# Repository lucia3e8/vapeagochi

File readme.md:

# tamagotchi that dies if you stop vaping
...has been rewritten in Rust. we also made it die if you _keep_ vaping. It counts how many times you've hit it and once you're at the dialy limit, turns off the heating coil.

## dirs
```
.
├── assets # animation sprites etc
├── case # fusion360 files for 3d-printed case
├── ee # kicad, components, assembly
├── readme.txt # you are here
├── scripts # one offs
├── vg2 # vestigial C++ stm32ide build
└── vgrs # new rust build <- USE THIS ONE
```

# Hardware
## Case
Initially we used a bc5000 vape because it's small and cute.
Right now bc5000 is too small to fit all the hardware, so we use a gimi30k instead.

Eventually I want to target the bc5000 because it's cuter but I'd have to redesign the PCB

## Pinout

```
| Pin  | Function        |
|------|-----------------|
| PA5  | SCREEN_CLK      |
| PA6  | SCREEN_RES      |
| PA7  | SCREEN_DIN      |
| PA8  | SCREEN_DC       |
| PB10 | SCREEN_CS       |
| PB3  | Left Button     |
| PA0  | Middle Button   |
| PB2  | Right Button    |
| PA4  | Coil Input      |
| PB11 | Coil Enable     |
| PA1  | Programmable LED|
```
By default, the vape's heating coil is disabled via a MOSFET. Pull `PB11 (Coil Enable)` high to allow the coil to turn on when user hits the vape.
When user tries to hit the vape, `PA4 (Coil Input)` will go high, regardless of `PB11` state.

# Software
## Building

Either use `nix-shell`, or manually install `cargo` with `thumbv6m-none-eabi` target and `probe-rs`.
```
cd vgrs
nix-shell
cargo build --release --target thumbv6m-none-eabi # build
sudo probe-rs run --chip STM32L072CBTx target/thumbv6m-none-eabi/release/vgrs # flash
```

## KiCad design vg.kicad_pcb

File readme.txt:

# Vapeagochi
## Building
linux only
run `mkdir -p build && make`
install stmcube programmer
run the programmer as root
under Erasing and Programming, pick your firmware.bin file
(you may have to first change the file owner to root because programmer is running as root)
set start address to 0x08000000
hit "Start Programming"

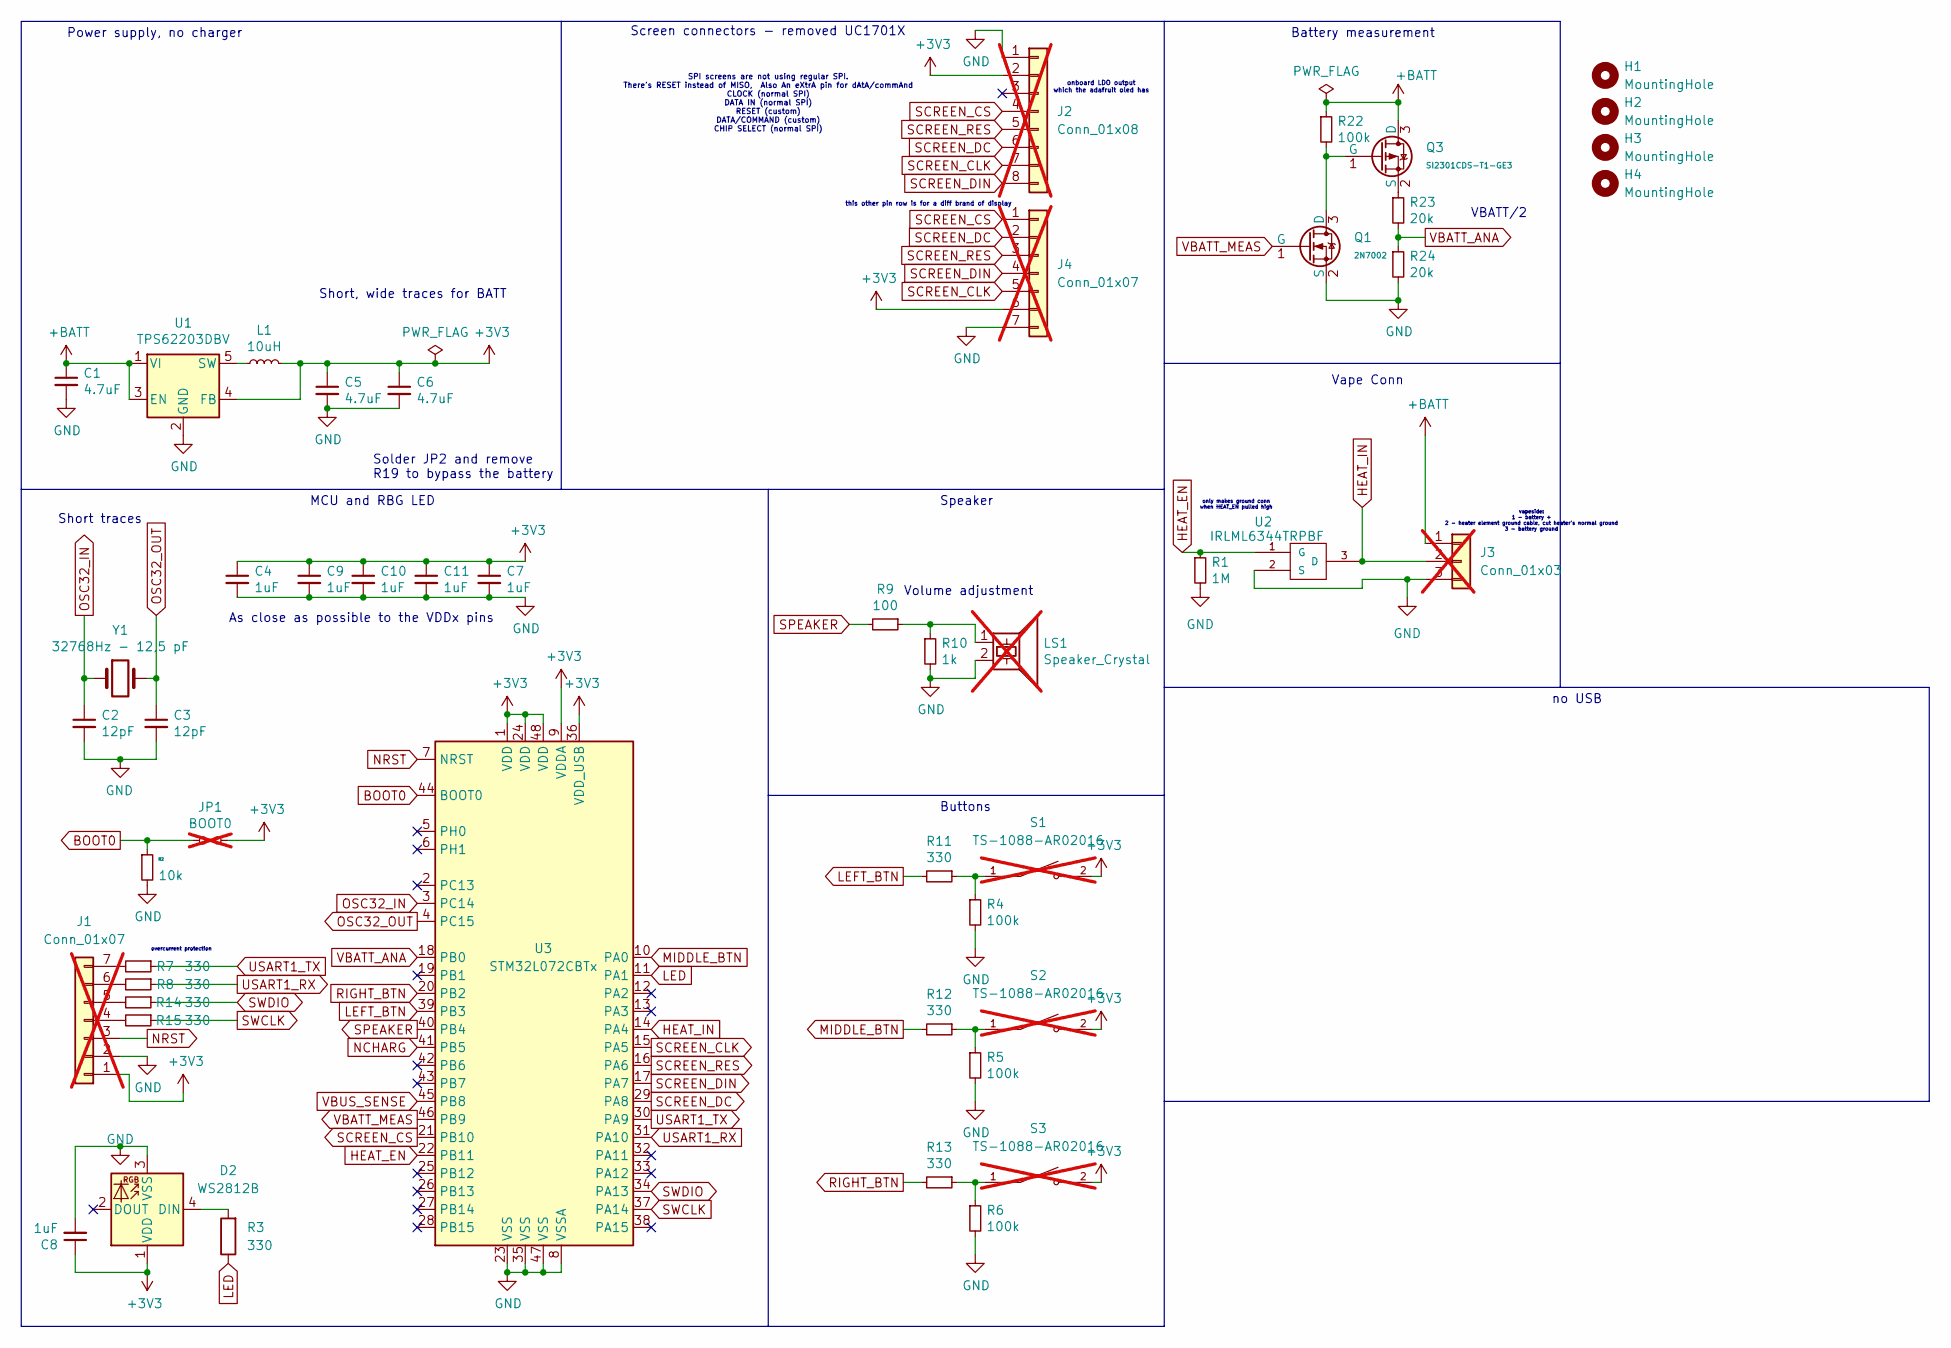
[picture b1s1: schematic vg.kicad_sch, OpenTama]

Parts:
C1, C5, C6: 4.7uF; C_0402_1005Metric; LCSC C23733
C2, C3: 12pF; C_0402_1005Metric; LCSC C1547
C4, C7, C8, C9, C10, C11: 1uF; C_0402_1005Metric; LCSC C52923
D2: WS2812B; LED_WS2812B_PLCC4_5.0x5.0mm_P3.2mm; LCSC C22461793
H1, H2, H3, H4: MountingHole; MountingHole_2.7mm_M2.5
J1, J4: Conn_01x07; PinHeader_1x07_P2.54mm_Vertical; not fitted
J2: Conn_01x08; PinHeader_1x08_P2.54mm_Vertical; not fitted
J3: Conn_01x03; JST_XH_S3B-XH-A_1x03_P2.50mm_Horizontal; not fitted
JP1: BOOT0; PinHeader_1x02_P2.54mm_Vertical; not fitted
L1: 10uH; L_0805_2012Metric; LCSC C1046
LS1: Speaker_Crystal; Buzzer_CUI_CPT-9019S-SMT; LCSC C391035; not fitted
Q1: 2N7002; Q_SOT-23; Part 2N7002; LCSC C8545
Q3: SI2301CDS-T1-GE3; Q_SOT-23; Part SI2301CDS-T1-GE3; LCSC C10487
R1: 1M; R_0402_1005Metric; LCSC C26083
R2: 10k; R_0402_1005Metric; LCSC C25744
R3: 330; R_0402_1005Metric
R4, R5, R6, R22: 100k; R_0402_1005Metric; LCSC C25741
R7, R8, R11, R12, R13, R14, R15: 330; R_0402_1005Metric; LCSC C25104
R9: 100; R_0805; LCSC C25076
R10: 1k; R_0402
R23, R24: 20k; R_0402_1005Metric; LCSC C25765
S1, S2, S3: TS-1088-AR02016; SW_TS-1088-AR02016; PARTREV N/A; LCSC C720477; not fitted
U1: TPS62203DBV; SOT-23-5; LCSC C9051
U2: IRLML6344TRPBF; SOT95P240X112-3N; MPN IRLML6344TRPBF
U3: STM32L072CBTx; LQFP-48_7x7mm_P0.5mm; LCSC C465977
Y1: 32768Hz - 12,5 pF; Crystal_SMD_3215-2Pin_3.2x1.5mm; LCSC C32346

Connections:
+3V3: C4.1, C5.1, C6.1, C7.1, C8.1, C9.1, C10.1, C11.1, D2.1 (VDD), J1.1, J2.2, J4.6, JP1.2, L1.2, S1.2, S2.2, S3.2, U1.4 (FB), U3.1 (VDD), U3.9 (VDDA), U3.24 (VDD), U3.36 (VDD_USB), U3.48 (VDD)
+BATT: C1.1, J3.1, Q3.3 (D), R22.1, U1.1 (VI), U1.3 (EN)
BOOT0: JP1.1, R2.1, U3.44 (BOOT0)
GND: C1.2, C2.2, C3.2, C4.2, C5.2, C6.2, C7.2, C8.2, C9.2, C10.2, C11.2, D2.3 (VSS), J1.2, J2.1, J3.3, J4.7, LS1.2, Q1.2 (S), R1.2, R2.2, R4.2, R5.2, R6.2, R10.2, R24.2, U1.2 (GND), U2.2 (S), U3.8 (VSSA), U3.23 (VSS), U3.35 (VSS), U3.47 (VSS)
HEAT_EN: R1.1, U2.1 (G), U3.22 (PB11)
HEAT_IN: J3.2, U2.3 (D), U3.14 (PA4)
LED: R3.1, U3.11 (PA1)
LEFT_BTN: R11.2, U3.39 (PB3)
MIDDLE_BTN: R12.2, U3.10 (PA0)
NCHARG: U3.41 (PB5)
NRST: J1.3, U3.7 (NRST)
unnamed: D2.4 (DIN), R3.2
unnamed: J1.4, R15.2
unnamed: J1.5, R14.2
unnamed: J1.6, R8.2
unnamed: J1.7, R7.2
unnamed: LS1.1, R9.1, R10.1
unnamed: Q1.3 (D), Q3.1 (G), R22.2
unnamed: Q3.2 (S), R23.1
unnamed: R4.1, R11.1, S1.1
unnamed: R5.1, R12.1, S2.1
unnamed: R6.1, R13.1, S3.1
unnamed: L1.1, U1.5 (SW)
OSC32_IN: C2.1, U3.3 (PC14), Y1.1
OSC32_OUT: C3.1, U3.4 (PC15), Y1.2
RIGHT_BTN: R13.2, U3.20 (PB2)
SCREEN_CLK: J2.7, J4.5, U3.15 (PA5)
SCREEN_CS: J2.4, J4.1, U3.21 (PB10)
SCREEN_DC: J2.6, J4.2, U3.29 (PA8)
SCREEN_DIN: J2.8, J4.4, U3.17 (PA7)
SCREEN_RES: J2.5, J4.3, U3.16 (PA6)
SPEAKER: R9.2, U3.40 (PB4)
SWCLK: R15.1, U3.37 (PA14)
SWDIO: R14.1, U3.34 (PA13)
USART1_RX: R8.1, U3.31 (PA10)
USART1_TX: R7.1, U3.30 (PA9)
VBATT_ANA: R23.2, R24.1, U3.18 (PB0)
VBATT_MEAS: Q1.1 (G), U3.46 (PB9)
VBUS_SENSE: U3.45 (PB8)

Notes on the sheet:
Power supply, no charger
Solder JP2 and remove R19 to bypass the battery
Short traces
onboard LDO output which the adafruit oled has
Short, wide traces for BATT
SPI screens are not using regular SPI. There's RESET instead of MISO, Also An eXtrA pin for dAtA/commAnd CLOCK (normal SPI) DATA IN (normal SPI) RESET (custom) DATA/COMMAND (custom) CHIP SELECT (normal SPI)
Battery measurement
this other pin row is for a diff brand of display
VBATT/2
Speaker
no USB
vapeside: 1 - battery + 2 - heater element ground cable, cut heater's normal ground 3 - battery ground
As close as possible to the VDDx pins
overcurrent protection
MCU and RBG LED
Vape Conn
only makes ground conn when HEAT_EN pulled high
Volume adjustment
Screen connectors - removed UC1701X
Buttons

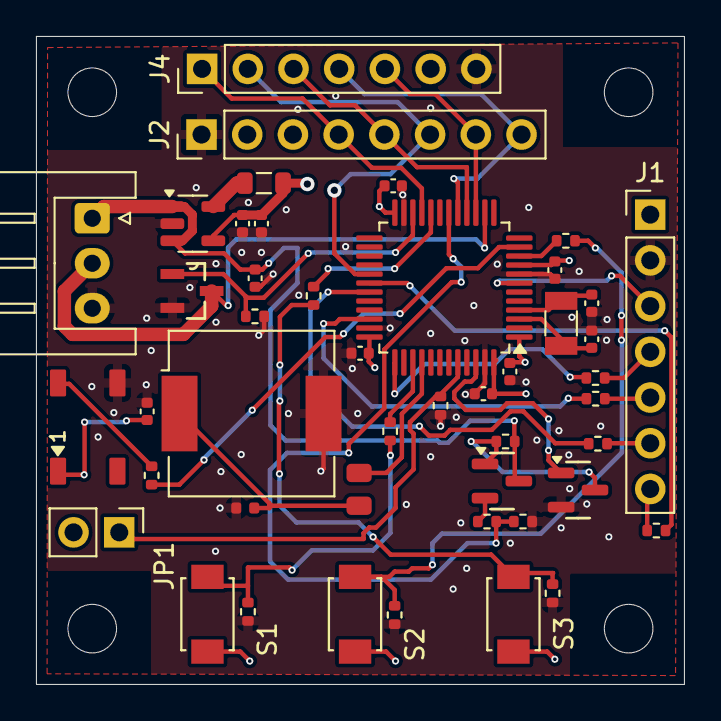
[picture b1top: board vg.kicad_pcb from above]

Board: 4 copper layers, 36.0 x 36.0 mm, 50 parts (0 on the bottom side), 37 nets.

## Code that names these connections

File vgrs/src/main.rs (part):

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    let gpioa = dp.GPIOA.split(&mut rcc);

    // Configure SPI pins
    let sck = gpioa.pa5;
    let mut rst = gpioa.pa6.into_push_pull_output();
    let mosi = gpioa.pa7;

    // hold chip select low the entire time, we only have 1 chip
    let mut cs = gpiob.pb10.into_push_pull_output();
    cs.set_low().unwrap();

    let dc = gpioa.pa8.into_push_pull_output();
    // Initialize SPI
    let spi = Spi::spi1(
        dp.SPI1,
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
    // ADC config
    let mut adc = Adc::new(dp.ADC, &mut rcc);
    let mut an_in = gpioa.pa4.into_analog(); // pin PA4 is HEAT_IN

    // coil enable/disable
    let mut coil_en = gpiob.pb11.into_push_pull_output();
    coil_en.set_high().unwrap(); // enables the heating coil

    // buttons!
    let btn_left = gpiob.pb3.into_floating_input();
    let btn_right = gpiob.pb2.into_floating_input();
    let btn_middle = gpioa.pa0.into_floating_input();

    let mut button_state = ButtonState::new();
    let mut voltage_state = VoltageState::new();
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
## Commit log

2024-12-11 add example stm32f072b files
2024-12-11 example build flow
2024-12-11 add stm32-ssd1306
2025-02-06 sprites
2025-02-06 png versions of assets
2025-02-06 python script to convert pngs into c structs
2025-02-06 demo that cycles 2 images
2025-02-06 gitignore
2025-02-06 other demo stuff
2025-02-06 idk what these do
2025-02-22 add stmide files
2025-02-22 update main.c:
2025-02-22 update ioc
2025-02-22 assets
2025-02-22 working prototype
2025-04-01 v0.2 pcb design, based on opentama
2025-04-02 add 2nd pin row
2025-04-05 dont pour all the way to the edge; replace speaker series cap with 0805 for better thermal; gnd vias on both sides of islands; long trace series resistors close to chip; shorter filter cap connections
2025-04-08 fix some LCSC #s
2025-05-05 update gitignore
2025-05-05 clean up
2025-05-05 format
2025-05-05 docs
2025-05-05 build instructions
2025-05-05 deps in readme
2025-05-06 coil readme
2025-05-12 add buttons, also rotate display
2025-05-12 hits up to 10
2025-05-16 no more flicker..........
2025-05-26 refactor hit count
2025-05-26 measure hit time instead
2025-05-26 persistent storage v1
2025-05-26 fixed persistent storage
2025-05-27 add hit count, limit, hourly reset button
2025-05-27 shut coil off
2025-05-27 put display in sleep mode when idle, wake up when hit or when buttons are pressed
2025-06-19 revert battery nonsense, fix the hitting logic
2025-08-15 add case, update readme
2025-11-12 remove c impl

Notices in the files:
ee/vg.kicad_sch:
Licensed under CERN-OHL-S v2
